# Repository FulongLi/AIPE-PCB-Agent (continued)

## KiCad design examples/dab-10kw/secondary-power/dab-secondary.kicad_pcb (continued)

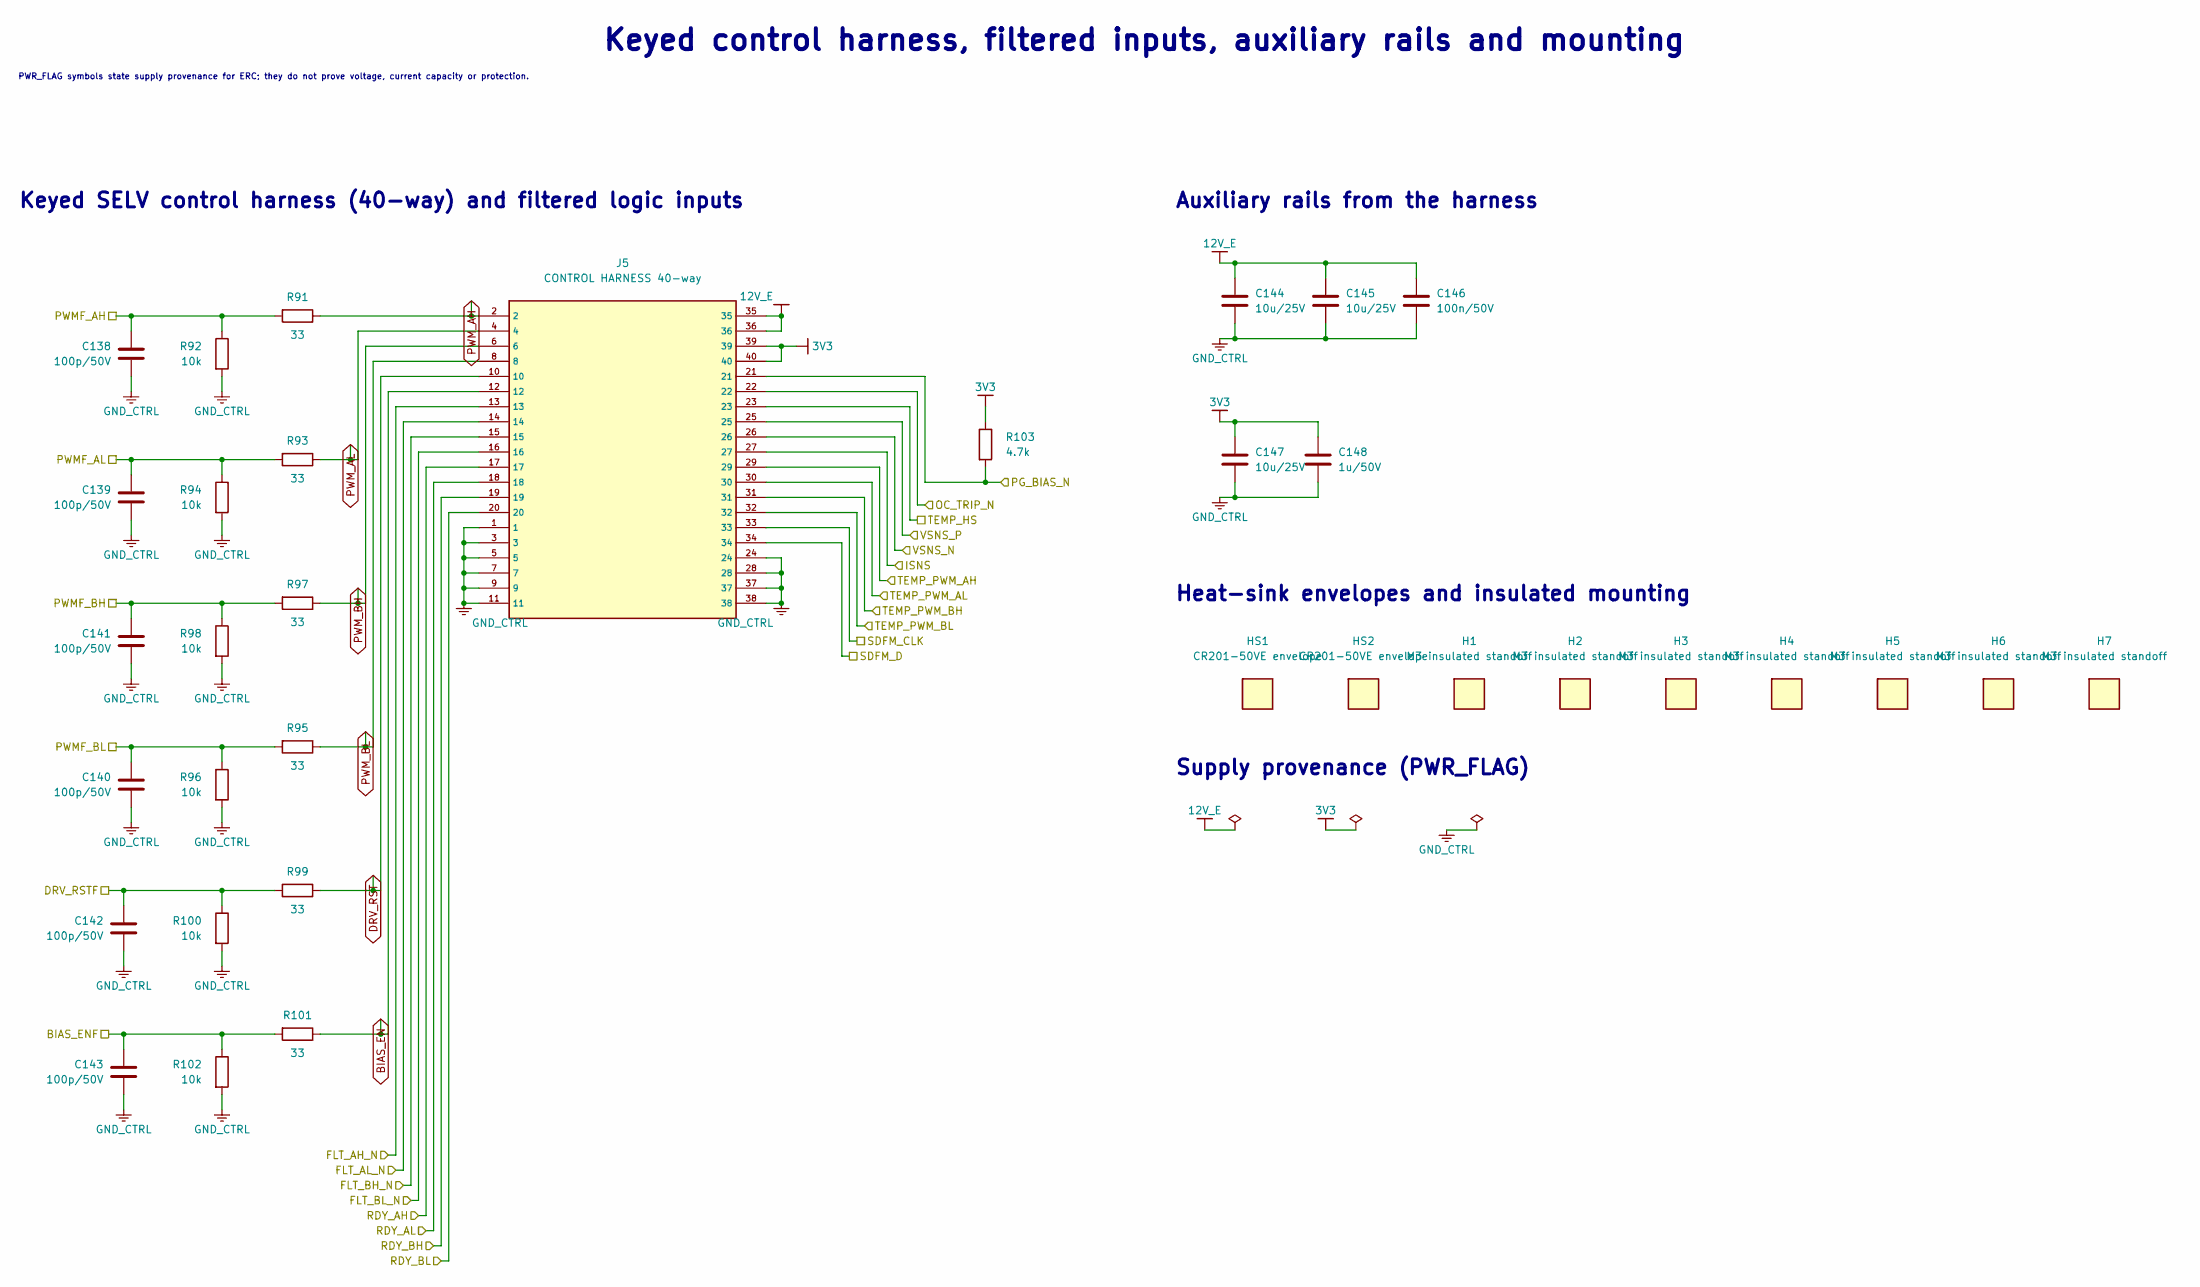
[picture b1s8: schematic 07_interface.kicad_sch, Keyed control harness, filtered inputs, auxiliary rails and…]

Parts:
C138, C139, C140, C141, C142, C143: 100p/50V; C_0603_1608Metric
C144, C145, C147: 10u/25V; C_1210_3225Metric
C146: 100n/50V; C_0603_1608Metric
C148: 1u/50V; C_0805_2012Metric
H1, H2, H3, H4, H5, H6, H7: M3 insulated standoff; MountingHole_3.2mm_M3
HS1, HS2: CR201-50VE envelope; DAB_HEATSINK_ENVELOPE
J5: CONTROL HARNESS 40-way; IDC-Header_2x20_P2.54mm_Vertical
R91, R93, R95, R97, R99, R101: 33; R_0603_1608Metric
R92, R94, R96, R98, R100, R102: 10k; R_0603_1608Metric
R103: 4.7k; R_0603_1608Metric

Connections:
3V3: C147.1, C148.1, J5.39, J5.40, R103.1; also elsewhere on the board
12V_E: C144.1, C145.1, C146.1, J5.35, J5.36; also elsewhere on the board
BIAS_EN: J5.12, R101.1
BIAS_ENF: C143.1, R101.2, R102.1; also elsewhere on the board
DRV_RST: J5.10, R99.1
DRV_RSTF: C142.1, R99.2, R100.1; also elsewhere on the board
FLT_AH_N: J5.13; also elsewhere on the board
FLT_AL_N: J5.14; also elsewhere on the board
FLT_BH_N: J5.15; also elsewhere on the board
FLT_BL_N: J5.16; also elsewhere on the board
GND_CTRL: C138.2, C139.2, C140.2, C141.2, C142.2, C143.2, C144.2, C145.2, C146.2, C147.2, C148.2, J5.1, J5.3, J5.5, J5.7, J5.9, J5.11, J5.24, J5.28, J5.37, J5.38, R92.2, R94.2, R96.2, R98.2, R100.2, R102.2; also elsewhere on the board
ISNS: J5.27; also elsewhere on the board
OC_TRIP_N: J5.22; also elsewhere on the board
PG_BIAS_N: J5.21, R103.2; also elsewhere on the board
PWMF_AH: C138.1, R91.2, R92.1; also elsewhere on the board
PWMF_AL: C139.1, R93.2, R94.1; also elsewhere on the board
PWMF_BH: C141.1, R97.2, R98.1; also elsewhere on the board
PWMF_BL: C140.1, R95.2, R96.1; also elsewhere on the board
PWM_AH: J5.2, R91.1
PWM_AL: J5.4, R93.1
PWM_BH: J5.6, R97.1
PWM_BL: J5.8, R95.1
RDY_AH: J5.17; also elsewhere on the board
RDY_AL: J5.18; also elsewhere on the board
RDY_BH: J5.19; also elsewhere on the board
RDY_BL: J5.20; also elsewhere on the board
SDFM_CLK: J5.33; also elsewhere on the board
SDFM_D: J5.34; also elsewhere on the board
TEMP_HS: J5.23; also elsewhere on the board
TEMP_PWM_AH: J5.29; also elsewhere on the board
TEMP_PWM_AL: J5.30; also elsewhere on the board
TEMP_PWM_BH: J5.31; also elsewhere on the board
TEMP_PWM_BL: J5.32; also elsewhere on the board
VSNS_N: J5.26; also elsewhere on the board
VSNS_P: J5.25; also elsewhere on the board

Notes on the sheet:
Keyed control harness, filtered inputs, auxiliary rails and mounting
PWR_FLAG symbols state supply provenance for ERC; they do not prove voltage, current capacity or protection.
Keyed SELV control harness (40-way) and filtered logic inputs
Auxiliary rails from the harness
Heat-sink envelopes and insulated mounting
Supply provenance (PWR_FLAG)

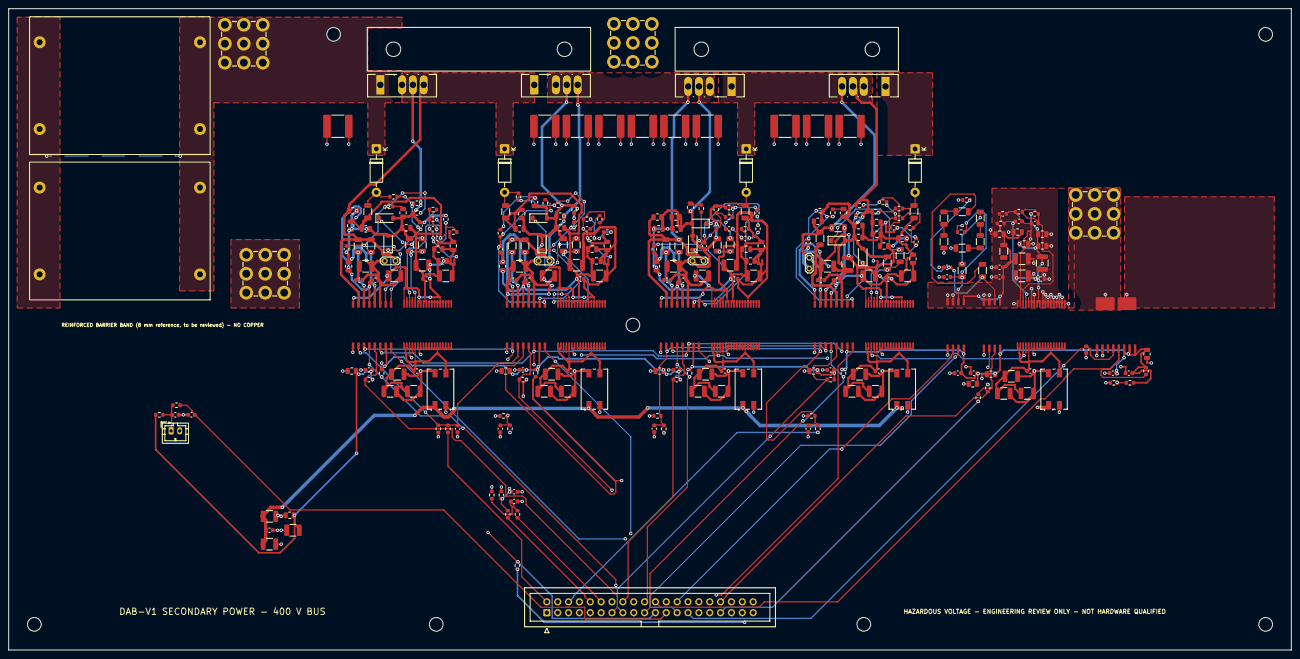
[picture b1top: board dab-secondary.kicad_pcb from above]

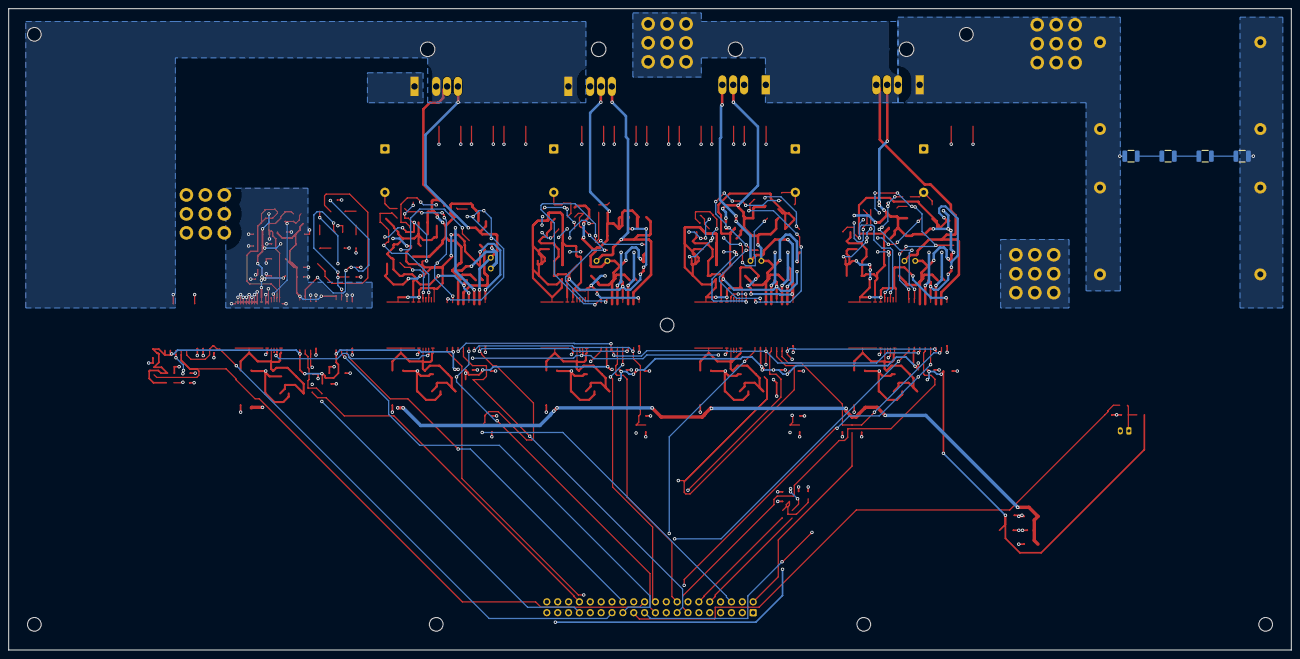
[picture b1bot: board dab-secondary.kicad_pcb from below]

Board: 4 copper layers, 300.0 x 150.0 mm, 312 parts (4 on the bottom side), 131 nets.

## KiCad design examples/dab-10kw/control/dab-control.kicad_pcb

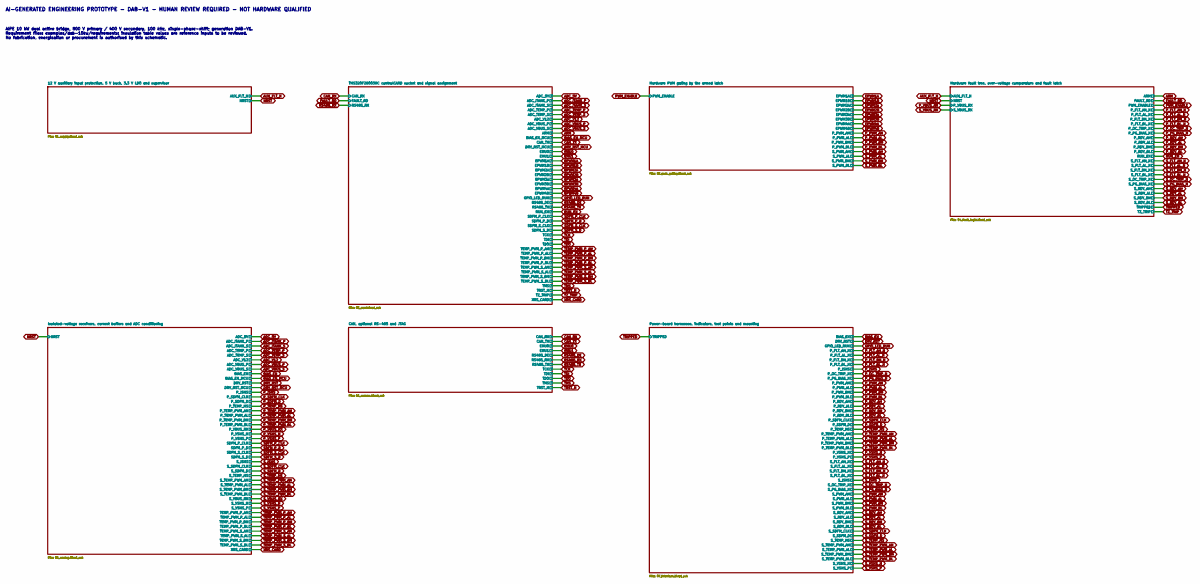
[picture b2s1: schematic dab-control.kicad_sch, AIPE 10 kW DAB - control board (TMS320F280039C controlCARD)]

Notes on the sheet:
AI-GENERATED ENGINEERING PROTOTYPE - DAB-V1 - HUMAN REVIEW REQUIRED - NOT HARDWARE QUALIFIED
AIPE 10 kW dual active bridge, 800 V primary / 400 V secondary, 100 kHz, single-phase-shift; generation DAB-V1. Requirement files: examples/dab-10kw/requirements; insulation table values are reference inputs to be reviewed. No fabrication, energisation or procurement is authorised by this schematic.

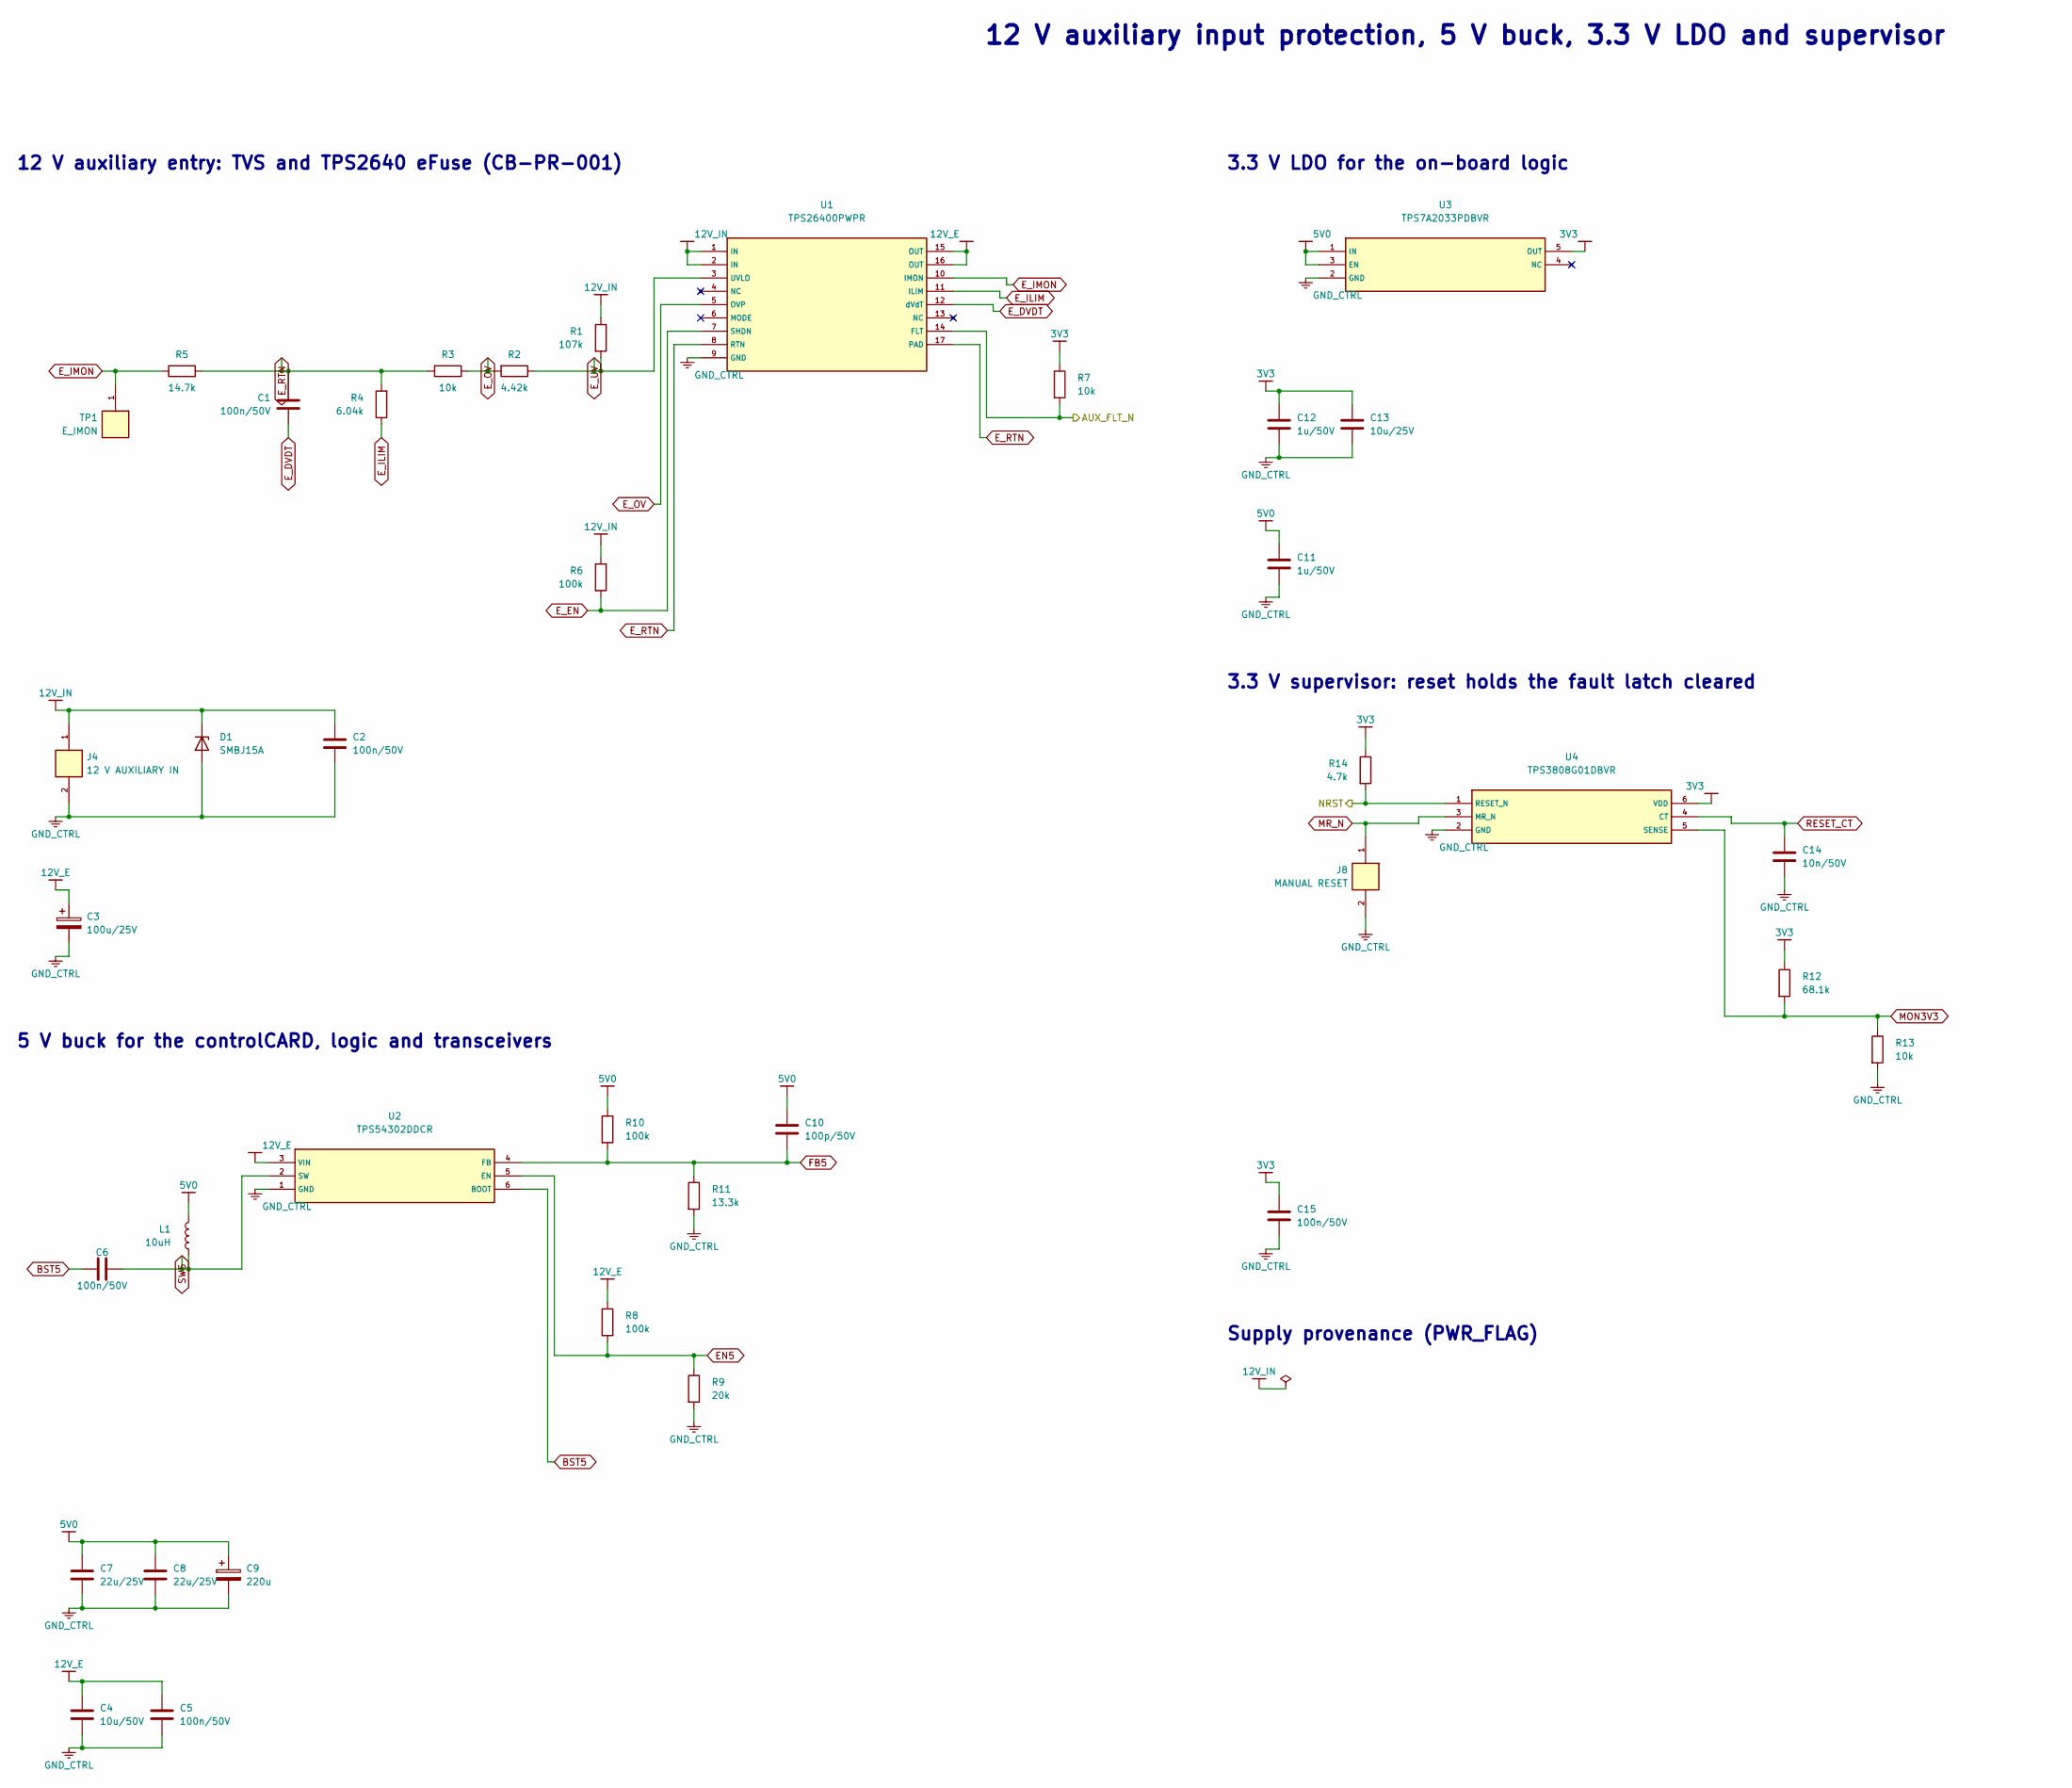
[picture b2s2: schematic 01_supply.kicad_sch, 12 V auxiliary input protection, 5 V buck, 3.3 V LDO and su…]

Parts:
C1, C2, C5, C6, C15: 100n/50V; C_0603_1608Metric
C3: 100u/25V; CP_Elec_8x10.5
C4: 10u/50V; C_1210_3225Metric
C7, C8: 22u/25V; C_1210_3225Metric
C9: 220u; CP_Radial_D6.3mm_P2.50mm
C10: 100p/50V; C_0603_1608Metric
C11, C12: 1u/50V; C_0805_2012Metric
C13: 10u/25V; C_1210_3225Metric
C14: 10n/50V; C_0603_1608Metric
D1: SMBJ15A; D_SMB
J4: 12 V AUXILIARY IN; PhoenixContact_MC_1,5_2-G-3.81_1x02_P3.81mm_Horizontal
J8: MANUAL RESET; PinHeader_1x02_P2.54mm_Vertical
L1: 10uH; L_Coilcraft_MSS1048-XXX
R1: 107k; R_0603_1608Metric
R2: 4.42k; R_0603_1608Metric
R3, R7, R13: 10k; R_0603_1608Metric
R4: 6.04k; R_0603_1608Metric
R5: 14.7k; R_0603_1608Metric
R6, R8, R10: 100k; R_0603_1608Metric
R9: 20k; R_0603_1608Metric
R11: 13.3k; R_0603_1608Metric
R12: 68.1k; R_0603_1608Metric
R14: 4.7k; R_0603_1608Metric
TP1: E_IMON; TestPoint_Pad_D1.0mm
U1: TPS26400PWPR; HTSSOP-16-1EP_4.4x5mm_P0.65mm_EP3.4x5mm
U2: TPS54302DDCR; SOT-23-6
U3: TPS7A2033PDBVR; SOT-23-5
U4: TPS3808G01DBVR; SOT-23-6

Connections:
3V3: C12.1, C13.1, C15.1, R7.1, R12.1, R14.1, U3.5 (OUT), U4.6 (VDD); also elsewhere on the board
5V0: C7.1, C8.1, C9.1, C10.1, C11.1, L1.2, R10.1, U3.1 (IN), U3.3 (EN); also elsewhere on the board
12V_E: C3.1, C4.1, C5.1, R8.1, U1.15 (OUT), U1.16 (OUT), U2.3 (VIN); also elsewhere on the board
12V_IN: C2.1, D1.1 (K), J4.1, R1.1, R6.1, U1.1 (IN), U1.2 (IN)
AUX_FLT_N: R7.2, U1.14 (FLT); also elsewhere on the board
BST5: C6.1, U2.6 (BOOT)
EN5: R8.2, R9.1, U2.5 (EN)
E_DVDT: C1.1, U1.12 (dVdT)
E_EN: R6.2, U1.7 (SHDN)
E_ILIM: R4.1, U1.11 (ILIM)
E_IMON: R5.1, TP1.1, U1.10 (IMON)
E_OV: R2.2, R3.1, U1.5 (OVP)
E_RTN: C1.2, R3.2, R4.2, R5.2, U1.8 (RTN), U1.17 (PAD)
E_UV: R1.2, R2.1, U1.3 (UVLO)
FB5: C10.2, R10.2, R11.1, U2.4 (FB)
GND_CTRL: C2.2, C3.2, C4.2, C5.2, C7.2, C8.2, C9.2, C11.2, C12.2, C13.2, C14.2, C15.2, D1.2 (A), J4.2, J8.2, R9.2, R11.2, R13.2, U1.9 (GND), U2.1 (GND), U3.2 (GND), U4.2 (GND); also elsewhere on the board
MON3V3: R12.2, R13.1, U4.5 (SENSE)
MR_N: J8.1, U4.3 (MR_N)
NRST: R14.2, U4.1 (RESET_N); also elsewhere on the board
RESET_CT: C14.1, U4.4 (CT)
SW5: C6.2, L1.1, U2.2 (SW)

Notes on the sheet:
12 V auxiliary input protection, 5 V buck, 3.3 V LDO and supervisor
12 V auxiliary entry: TVS and TPS2640 eFuse (CB-PR-001)
5 V buck for the controlCARD, logic and transceivers
3.3 V LDO for the on-board logic
3.3 V supervisor: reset holds the fault latch cleared
Supply provenance (PWR_FLAG)

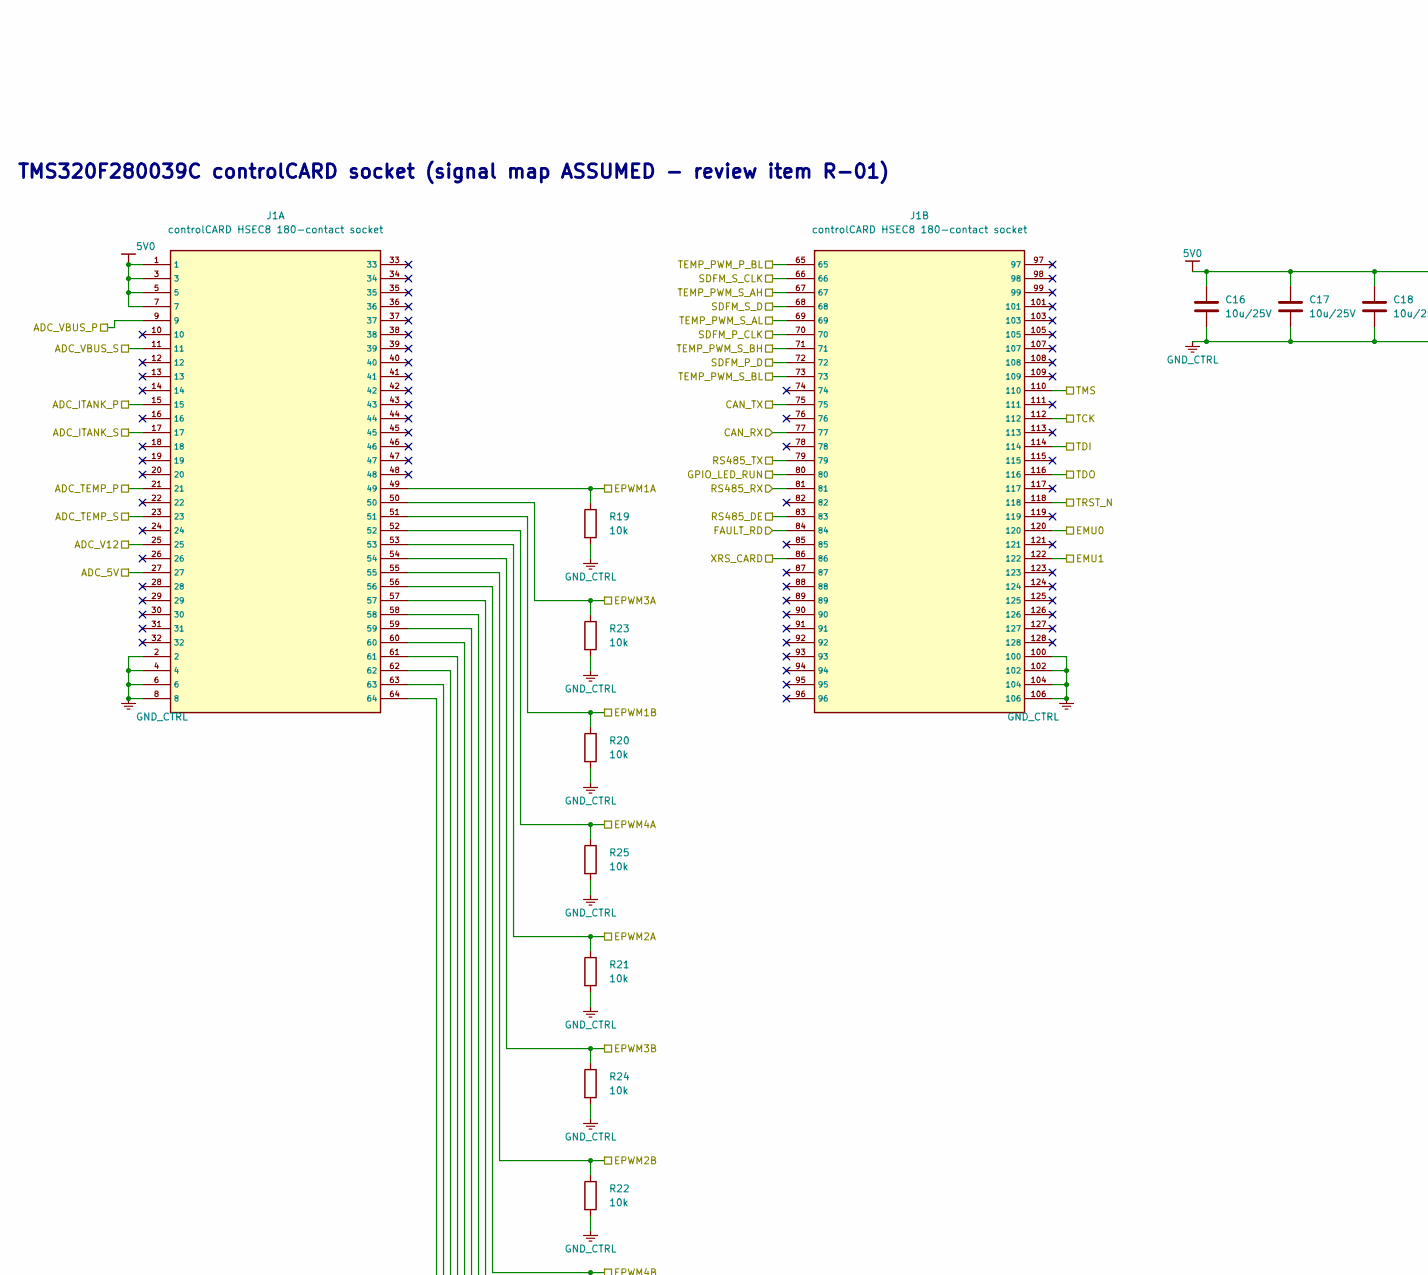
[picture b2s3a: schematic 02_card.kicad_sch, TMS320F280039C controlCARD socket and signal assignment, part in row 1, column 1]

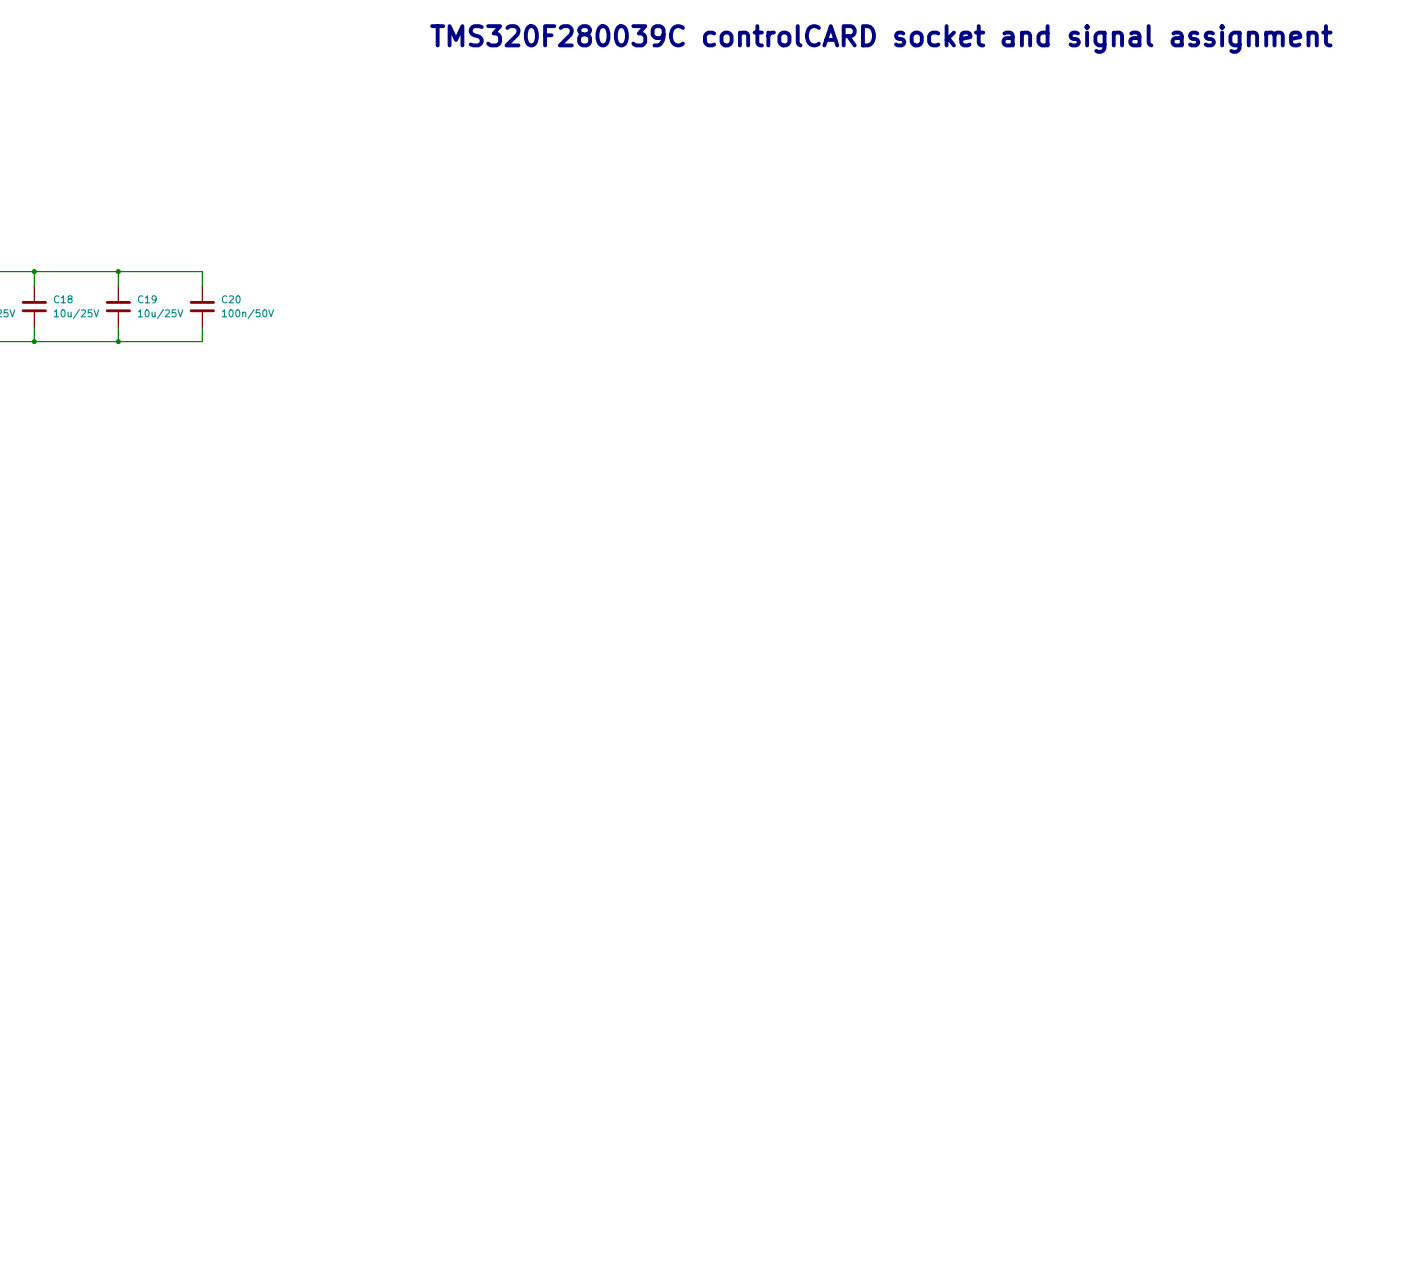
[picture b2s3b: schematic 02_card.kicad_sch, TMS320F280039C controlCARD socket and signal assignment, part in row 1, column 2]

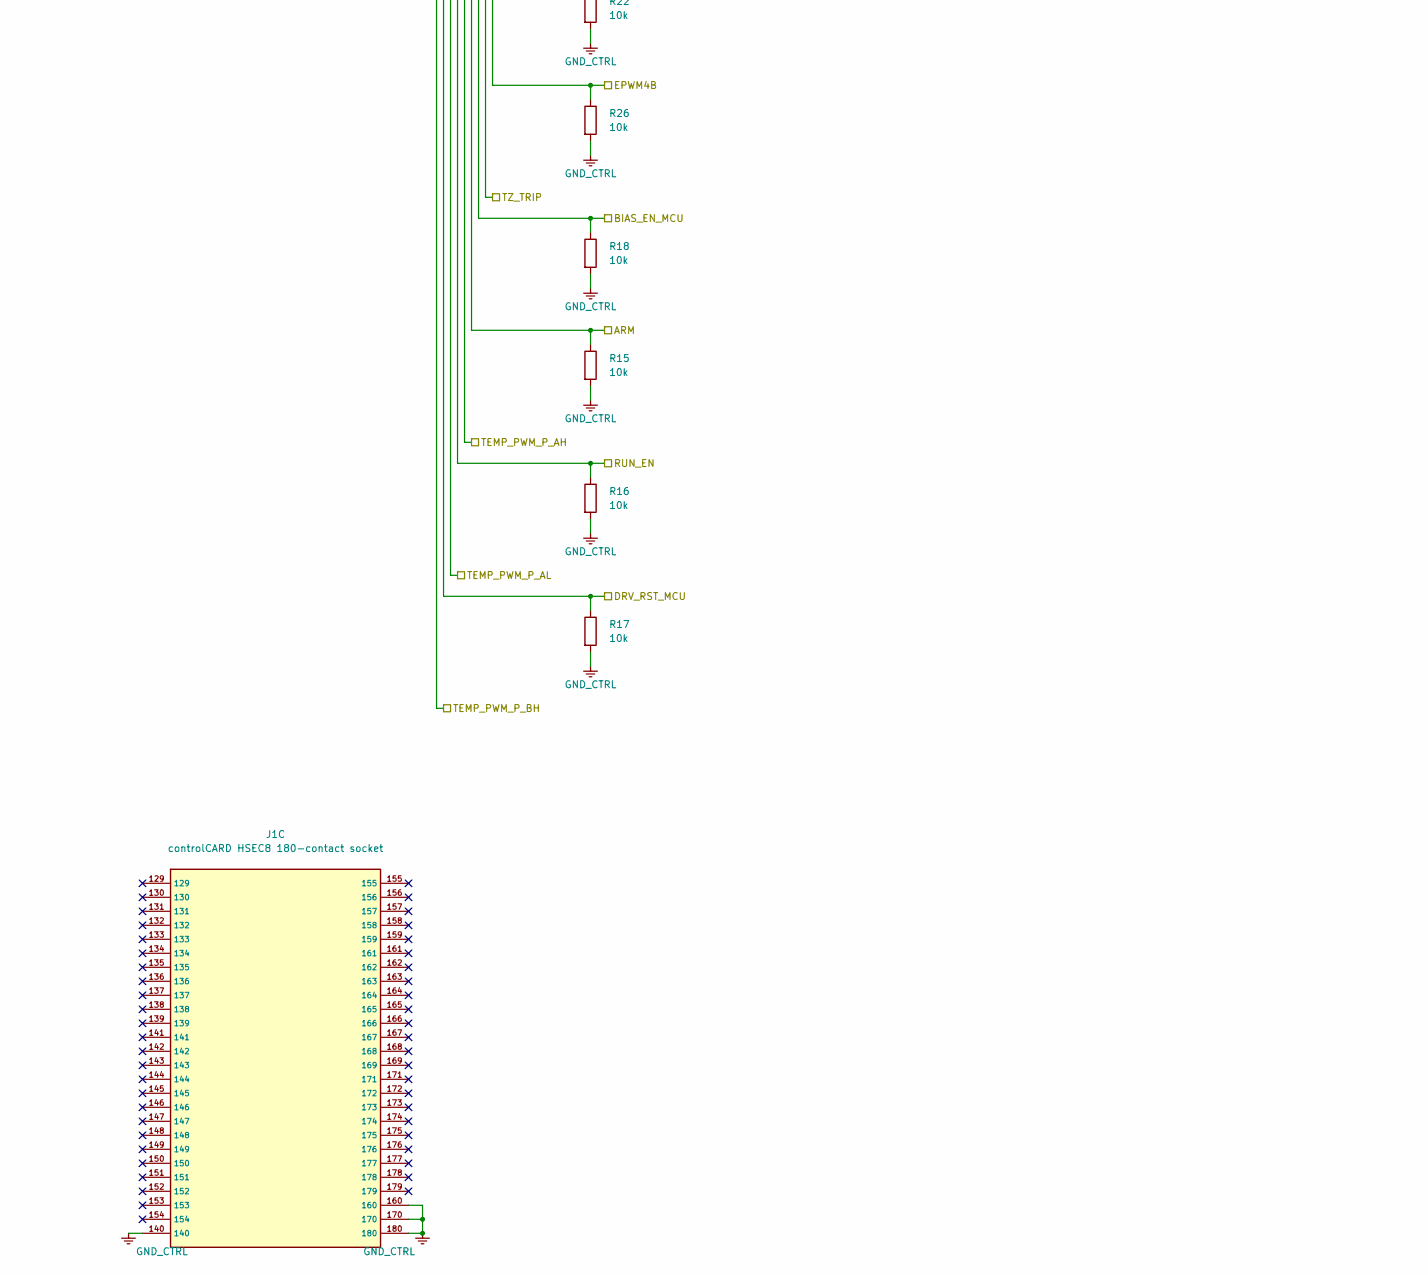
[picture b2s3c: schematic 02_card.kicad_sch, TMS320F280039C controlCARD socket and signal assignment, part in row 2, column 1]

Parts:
C16, C17, C18, C19: 10u/25V; C_1210_3225Metric
C20: 100n/50V; C_0603_1608Metric
J1: controlCARD HSEC8 180-contact socket; Samtec_HSEC8-190-01-X-DV-A_2x90_P0.8mm_Pol32_Socket_Alignme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
R15, R16, R17, R18, R19, R20, R21, R22, R23, R24, R25, R26: 10k; R_0603_1608Metric

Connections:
5V0: C16.1, C17.1, C18.1, C19.1, C20.1, J1.1, J1.3, J1.5, J1.7; also elsewhere on the board
ADC_5V: J1.27; also elsewhere on the board
ADC_ITANK_P: J1.15; also elsewhere on the board
ADC_ITANK_S: J1.17; also elsewhere on the board
ADC_TEMP_P: J1.21; also elsewhere on the board
ADC_TEMP_S: J1.23; also elsewhere on the board
ADC_V12: J1.25; also elsewhere on the board
ADC_VBUS_P: J1.9; also elsewhere on the board
ADC_VBUS_S: J1.11; also elsewhere on the board
ARM: J1.59, R15.1; also elsewhere on the board
BIAS_EN_MCU: J1.58, R18.1; also elsewhere on the board
CAN_RX: J1.77; also elsewhere on the board
CAN_TX: J1.75; also elsewhere on the board
DRV_RST_MCU: J1.63, R17.1; also elsewhere on the board
EMU0: J1.120; also elsewhere on the board
EMU1: J1.122; also elsewhere on the board
EPWM1A: J1.49, R19.1; also elsewhere on the board
EPWM1B: J1.51, R20.1; also elsewhere on the board
EPWM2A: J1.53, R21.1; also elsewhere on the board
EPWM2B: J1.55, R22.1; also elsewhere on the board
EPWM3A: J1.50, R23.1; also elsewhere on the board
EPWM3B: J1.54, R24.1; also elsewhere on the board
EPWM4A: J1.52, R25.1; also elsewhere on the board
EPWM4B: J1.56, R26.1; also elsewhere on the board
FAULT_RD: J1.84; also elsewhere on the board
GND_CTRL: C16.2, C17.2, C18.2, C19.2, C20.2, J1.2, J1.4, J1.6, J1.8, J1.100, J1.102, J1.104, J1.106, J1.140, J1.160, J1.170, J1.180, R15.2, R16.2, R17.2, R18.2, R19.2, R20.2, R21.2, R22.2, R23.2, R24.2, R25.2, R26.2; also elsewhere on the board
GPIO_LED_RUN: J1.80; also elsewhere on the board
RS485_DE: J1.83; also elsewhere on the board
RS485_RX: J1.81; also elsewhere on the board
RS485_TX: J1.79; also elsewhere on the board
RUN_EN: J1.61, R16.1; also elsewhere on the board
SDFM_P_CLK: J1.70; also elsewhere on the board
SDFM_P_D: J1.72; also elsewhere on the board
SDFM_S_CLK: J1.66; also elsewhere on the board
SDFM_S_D: J1.68; also elsewhere on the board
TCK: J1.112; also elsewhere on the board
TDI: J1.114; also elsewhere on the board
TDO: J1.116; also elsewhere on the board
TEMP_PWM_P_AH: J1.60; also elsewhere on the board
TEMP_PWM_P_AL: J1.62; also elsewhere on the board
TEMP_PWM_P_BH: J1.64; also elsewhere on the board
TEMP_PWM_P_BL: J1.65; also elsewhere on the board
TEMP_PWM_S_AH: J1.67; also elsewhere on the board
TEMP_PWM_S_AL: J1.69; also elsewhere on the board
TEMP_PWM_S_BH: J1.71; also elsewhere on the board
TEMP_PWM_S_BL: J1.73; also elsewhere on the board
TMS: J1.110; also elsewhere on the board
TRST_N: J1.118; also elsewhere on the board
TZ_TRIP: J1.57; also elsewhere on the board
XRS_CARD: J1.86; also elsewhere on the board

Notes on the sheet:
TMS320F280039C controlCARD socket and signal assignment
TMS320F280039C controlCARD socket (signal map ASSUMED - review item R-01)

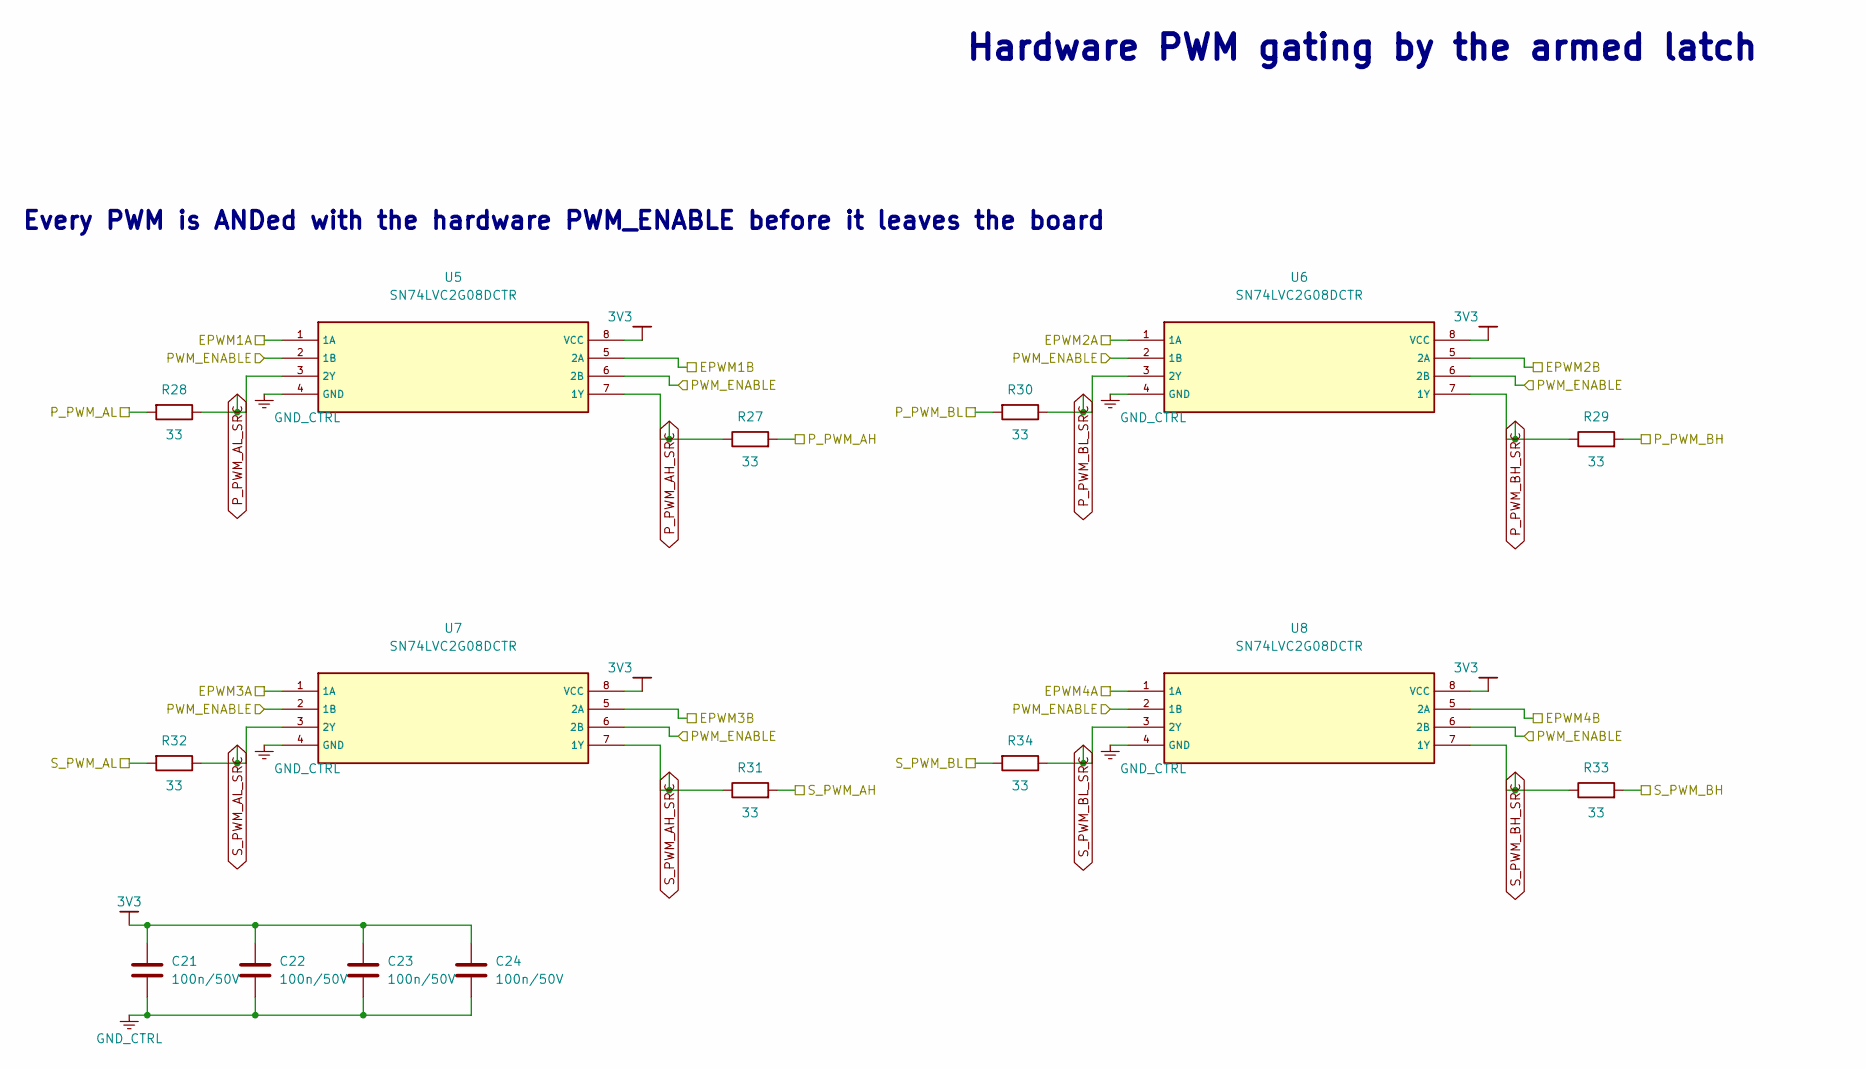
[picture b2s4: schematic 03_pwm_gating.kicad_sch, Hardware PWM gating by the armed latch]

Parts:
C21, C22, C23, C24: 100n/50V; C_0603_1608Metric
R27, R28, R29, R30, R31, R32, R33, R34: 33; R_0603_1608Metric
U5, U6, U7, U8: SN74LVC2G08DCTR; SSOP-8_2.95x2.8mm_P0.65mm

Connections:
3V3: C21.1, C22.1, C23.1, C24.1, U5.8 (VCC), U6.8 (VCC), U7.8 (VCC), U8.8 (VCC); also elsewhere on the board
EPWM1A: U5.1 (1A); also elsewhere on the board
EPWM1B: U5.5 (2A); also elsewhere on the board
EPWM2A: U6.1 (1A); also elsewhere on the board
EPWM2B: U6.5 (2A); also elsewhere on the board
EPWM3A: U7.1 (1A); also elsewhere on the board
EPWM3B: U7.5 (2A); also elsewhere on the board
EPWM4A: U8.1 (1A); also elsewhere on the board
EPWM4B: U8.5 (2A); also elsewhere on the board
GND_CTRL: C21.2, C22.2, C23.2, C24.2, U5.4 (GND), U6.4 (GND), U7.4 (GND), U8.4 (GND); also elsewhere on the board
PWM_ENABLE: U5.2 (1B), U5.6 (2B), U6.2 (1B), U6.6 (2B), U7.2 (1B), U7.6 (2B), U8.2 (1B), U8.6 (2B); also elsewhere on the board
P_PWM_AH: R27.2; also elsewhere on the board
P_PWM_AH_SRC: R27.1, U5.7 (1Y)
P_PWM_AL: R28.2; also elsewhere on the board
P_PWM_AL_SRC: R28.1, U5.3 (2Y)
P_PWM_BH: R29.2; also elsewhere on the board
P_PWM_BH_SRC: R29.1, U6.7 (1Y)
P_PWM_BL: R30.2; also elsewhere on the board
P_PWM_BL_SRC: R30.1, U6.3 (2Y)
S_PWM_AH: R31.2; also elsewhere on the board
S_PWM_AH_SRC: R31.1, U7.7 (1Y)
S_PWM_AL: R32.2; also elsewhere on the board
S_PWM_AL_SRC: R32.1, U7.3 (2Y)
S_PWM_BH: R33.2; also elsewhere on the board
S_PWM_BH_SRC: R33.1, U8.7 (1Y)
S_PWM_BL: R34.2; also elsewhere on the board
S_PWM_BL_SRC: R34.1, U8.3 (2Y)

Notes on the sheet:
Hardware PWM gating by the armed latch
Every PWM is ANDed with the hardware PWM_ENABLE before it leaves the board
